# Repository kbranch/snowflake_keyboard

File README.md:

# Snowflake Keyboard

This is a weird, tightly spaced split keyboard that I designed to be very specific to my needs. It uses 17x16 mm key spacing rather than the standard 19x19 mm (inspired by [this post](https://www.reddit.com/r/ErgoMechKeyboards/comments/hudjyt/current_research_on_ergonomics_keyboard_design/)). The odd keys on the outside bottom corners are meant to be pressed with the pinky's knuckle rather than a fingertip. I haven't included every detail necessary to build the whole keyboard since it's so specific to my needs, but I'm happy to share and/or answer questions if somebody is interested in more detail for some reason.

The original CAD files are public on OnShape: [Case](https://cad.onshape.com/documents/9b32c1e8e8106ea44925f1b6/w/90cc6aeac4d327d0808a83e7/e/3e782787b37f9a3620b3203b) and [Keycaps](https://cad.onshape.com/documents/7a9b7e869b26a13f2521e861/w/94ad519ba1de32380f27d44b/e/4a5e31582eda700c8368bdb9). Generating the keycap legends is a pretty manual and sometimes fiddly process. I believe I included copies of all of the STLs I used, but I may have forgotten a few. 3mf files are included for the keycaps and legends, which should load into PrusaSlicer with all models in their correct quantities and print settings ready to go for a Prusa i3 MK3S.

All 3D printed parts are designed to be printed without support. I used manual mid-print color changes to embed the LED diffuser pieces into the case and for the keycap legends. M2 screws and nuts hold the PCB and plate to the case, and M3 screws and nuts hold the case halves and palm rests together. Little o-rings sit between the plate and case.

I used USB-C for both the actual USB connector and the board to board connection. I repurposed some [USB-A to USB-C adapters](https://www.amazon.com/gp/product/B07VCZV3R4/ref=ppx_yo_dt_b_asin_title_o09_s00?ie=UTF8&psc=1) to use as panel mount USB-C connectors. I ended up needing to grind the fronts down a bit to allow for cables to snap in fully through the case thickness.

The referenced QMK version includes a small tweak to allow the brightness of the indicator LEDs to follow the regular LED animation brightness. The LEDs are set up to indicate the active layer and the status of num, caps and scroll lock - they're not intended for flashy animations.

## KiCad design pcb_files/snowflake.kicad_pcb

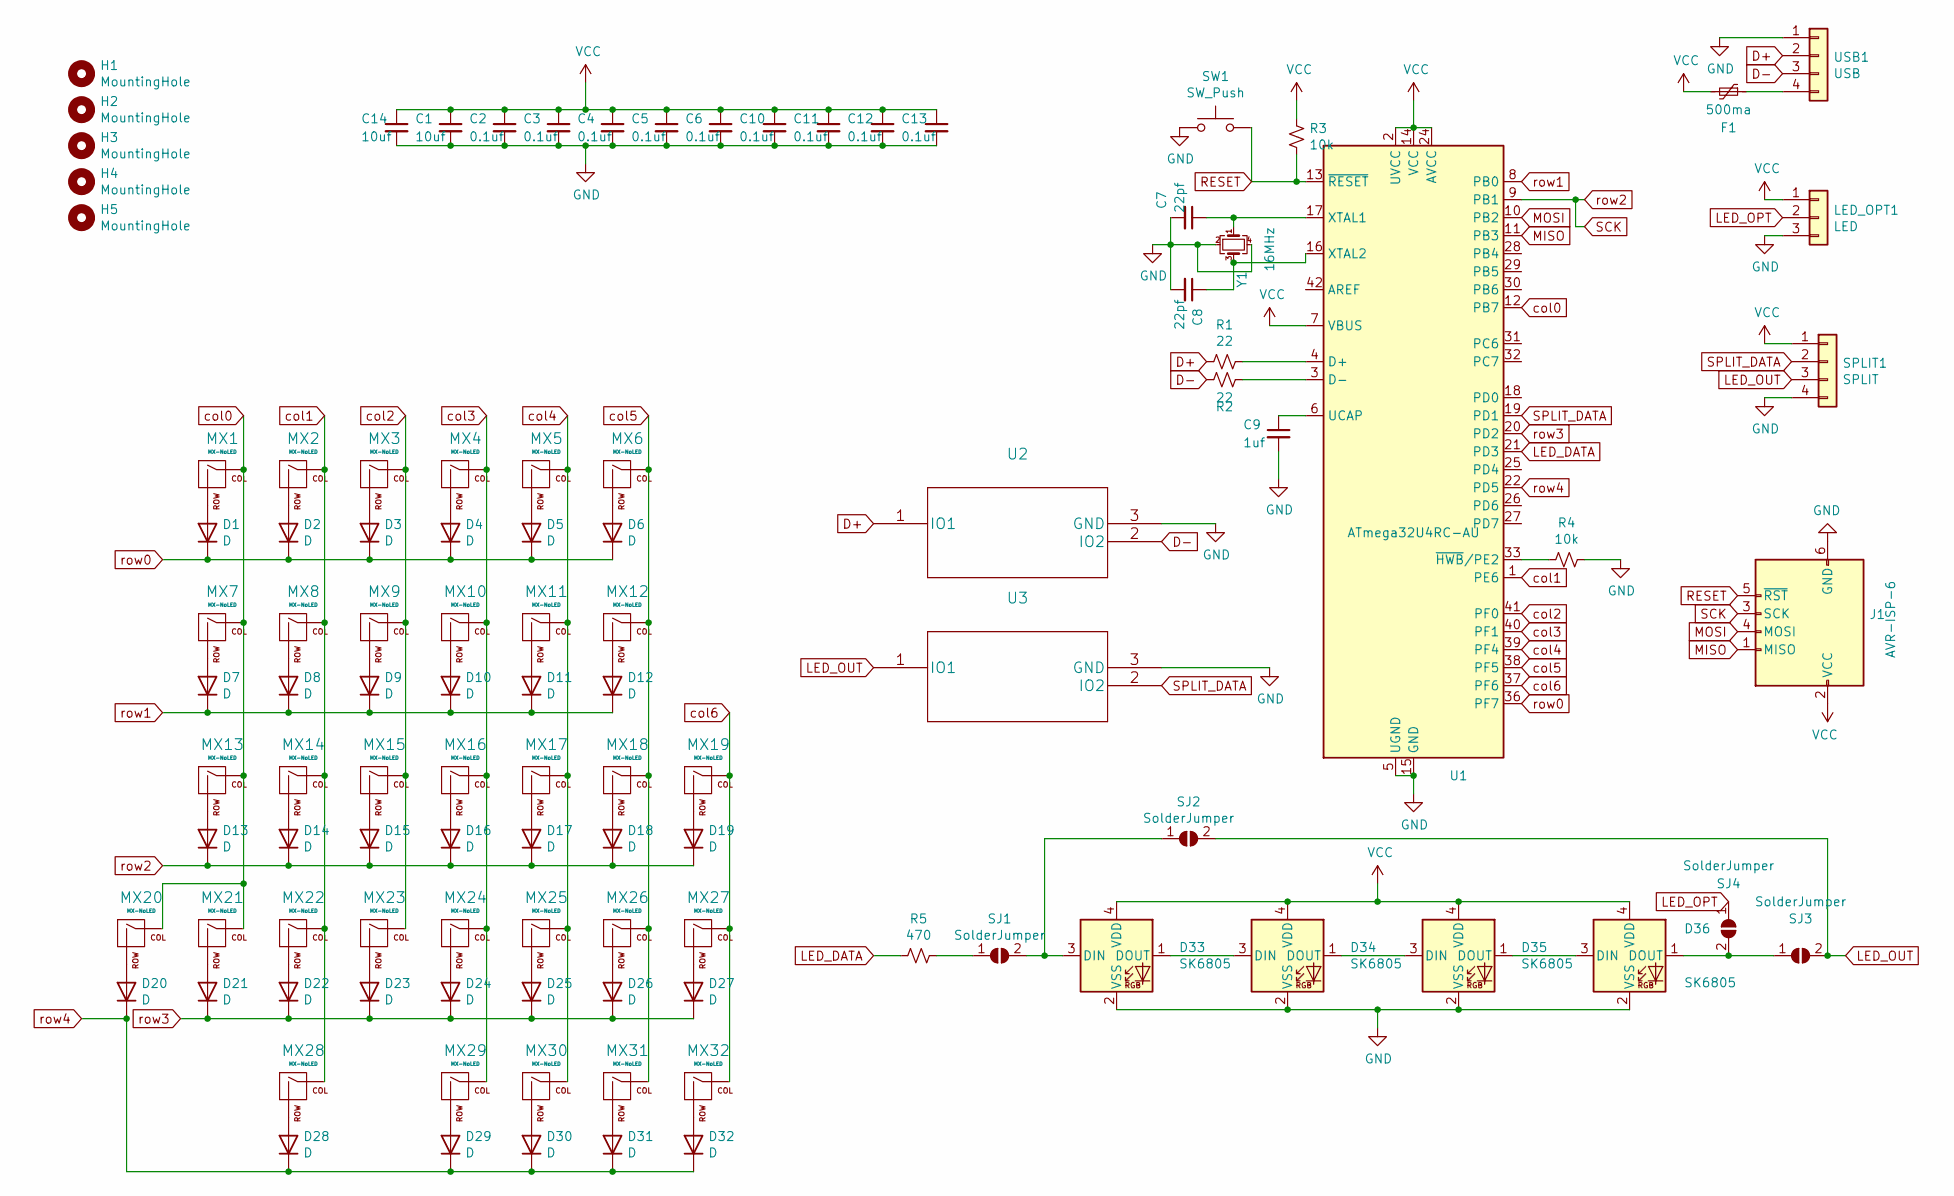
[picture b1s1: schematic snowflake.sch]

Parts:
C1, C14: 10uf; C_0603_1608Metric_Pad1.08x0.95mm_HandSolder
C2, C3, C4, C5, C6, C10, C11, C12, C13: 0.1uf; C_0603_1608Metric_Pad1.08x0.95mm_HandSolder
C7, C8: 22pf; C_0603_1608Metric_Pad1.08x0.95mm_HandSolder
C9: 1uf; C_0603_1608Metric_Pad1.08x0.95mm_HandSolder
D1, D2, D3, D4, D5, D6, D7, D8, D9, D10, D11, D12, D13, D14, D15, D16, D17, D18, D19, D20, D21, D22, D23, D24, D25, D26, D27, D28, D29, D30, D31, D32: D; D_SOD-123
D33, D34, D35, D36: SK6805; LED_SK6805_PLCC4_2.4x2.7mm_P1.3mm
F1: 500ma; Fuse_0805_2012Metric_Castellated
H1, H2, H3, H4, H5: MountingHole; MountingHole_2.2mm_M2
J1: AVR-ISP-6; PinHeader_2x03_P2.54mm_Vertical
LED_OPT1: LED; PinHeader_1x03_P2.54mm_Horizontal
MX1, MX2, MX3, MX4, MX5, MX6, MX7, MX8, MX9, MX10, MX11, MX12, MX13, MX14, MX15, MX16, MX17, MX18, MX19, MX20, MX21, MX22, MX23, MX24, MX25, MX26, MX27, MX28, MX29, MX30, MX31, MX32: MX-NoLED; Kailh_socket_MX
R1, R2: 22; R_0603_1608Metric_Pad0.98x0.95mm_HandSolder
R3, R4: 10k; R_0603_1608Metric_Pad0.98x0.95mm_HandSolder
R5: 470; R_0603_1608Metric_Pad0.98x0.95mm_HandSolder
SJ1, SJ2, SJ3, SJ4: SolderJumper; SolderJumper-2_P1.3mm_Open_RoundedPad1.0x1.5mm
SPLIT1: SPLIT; PinHeader_1x04_P2.54mm_Horizontal
SW1: SW_Push; SW_Push_SPST_NO_Alps_SKRK
U1: ATmega32U4RC-AU; TQFP-44_10x10mm_P0.8mm
U2, U3: TPD2E2U06DCKR
USB1: USB; PinHeader_1x04_P2.54mm_Horizontal
Y1: 16MHz; Crystal_SMD_3225-4Pin_3.2x2.5mm_HandSoldering

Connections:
D+: R1.2, U2.1 (IO1), USB1.2
D-: R2.2, U2.2 (IO2), USB1.3
GND: C1.2, C2.2, C3.2, C4.2, C5.2, C6.2, C7.2, C8.2, C9.2, C10.2, C11.2, C12.2, C13.2, C14.2, D33.2 (VSS), D34.2 (VSS), D35.2 (VSS), D36.2 (VSS), J1.6 (GND), LED_OPT1.3, R4.1, SPLIT1.4, SW1.1, U1.5 (UGND), U1.15 (GND), U1.23 (GND), U1.35 (GND), U1.43 (GND), U2.3 (GND), U3.3 (GND), USB1.1, Y1.2, Y1.4; also elsewhere on the board
LED_DATA: R5.2, U1.21 (PD3)
LED_OPT: LED_OPT1.2, SJ4.1 (A)
LED_OUT: SJ2.2 (B), SJ3.2 (B), SPLIT1.3, U3.1 (IO1)
MISO: J1.1 (MISO), U1.11 (PB3); also elsewhere on the board
MOSI: J1.4 (MOSI), U1.10 (PB2); also elsewhere on the board
unnamed: C7.1, U1.17 (XTAL1), Y1.1
unnamed: C8.1, U1.16 (XTAL2), Y1.3
unnamed: C9.1, U1.6 (UCAP)
unnamed: D1.2 (A), MX1.2 (ROW)
unnamed: D2.2 (A), MX2.2 (ROW)
unnamed: D3.2 (A), MX3.2 (ROW)
unnamed: D4.2 (A), MX4.2 (ROW)
unnamed: D5.2 (A), MX5.2 (ROW)
unnamed: D6.2 (A), MX6.2 (ROW)
unnamed: D7.2 (A), MX7.2 (ROW)
unnamed: D8.2 (A), MX8.2 (ROW)
unnamed: D9.2 (A), MX9.2 (ROW)
unnamed: D10.2 (A), MX10.2 (ROW)
unnamed: D11.2 (A), MX11.2 (ROW)
unnamed: D12.2 (A), MX12.2 (ROW)
unnamed: D13.2 (A), MX13.2 (ROW)
unnamed: D14.2 (A), MX14.2 (ROW)
unnamed: D15.2 (A), MX15.2 (ROW)
unnamed: D16.2 (A), MX16.2 (ROW)
unnamed: D17.2 (A), MX17.2 (ROW)
unnamed: D18.2 (A), MX18.2 (ROW)
unnamed: D19.2 (A), MX19.2 (ROW)
unnamed: D20.2 (A), MX20.2 (ROW)
unnamed: D21.2 (A), MX21.2 (ROW)
unnamed: D22.2 (A), MX22.2 (ROW)
unnamed: D23.2 (A), MX23.2 (ROW)
unnamed: D24.2 (A), MX24.2 (ROW)
unnamed: D25.2 (A), MX25.2 (ROW)
unnamed: D26.2 (A), MX26.2 (ROW)
unnamed: D27.2 (A), MX27.2 (ROW)
unnamed: D28.2 (A), MX28.2 (ROW)
unnamed: D29.2 (A), MX29.2 (ROW)
unnamed: D30.2 (A), MX30.2 (ROW)
unnamed: D31.2 (A), MX31.2 (ROW)
unnamed: D32.2 (A), MX32.2 (ROW)
unnamed: D33.1 (DOUT), D34.3 (DIN)
unnamed: D33.3 (DIN), SJ1.2 (B), SJ2.1 (A)
unnamed: D34.1 (DOUT), D35.3 (DIN)
unnamed: D35.1 (DOUT), D36.3 (DIN)
unnamed: D36.1 (DOUT), SJ3.1 (A), SJ4.2 (B)
unnamed: F1.1, USB1.4
unnamed: R1.1, U1.4 (D+)
unnamed: R2.1, U1.3 (D-)
unnamed: R4.2, U1.33 (~HWB~/PE2)
unnamed: R5.1, SJ1.1 (A)
RESET: J1.5 (~RST), R3.1, SW1.2, U1.13 (~RESET); also elsewhere on the board
SCK: D13.1 (K), D14.1 (K), D15.1 (K), D16.1 (K), D17.1 (K), D18.1 (K), D19.1 (K), J1.3 (SCK), U1.9 (PB1); also elsewhere on the board
SPLIT_DATA: SPLIT1.2, U1.19 (PD1), U3.2 (IO2)
VCC: C1.1, C2.1, C3.1, C4.1, C5.1, C6.1, C10.1, C11.1, C12.1, C13.1, C14.1, D33.4 (VDD), D34.4 (VDD), D35.4 (VDD), D36.4 (VDD), F1.2, J1.2 (VCC), LED_OPT1.1, R3.2, SPLIT1.1, U1.2 (UVCC), U1.7 (VBUS), U1.14 (VCC), U1.24 (AVCC), U1.34 (VCC), U1.44 (AVCC); also elsewhere on the board
col0: MX1.1 (COL), MX7.1 (COL), MX13.1 (COL), MX20.1 (COL), MX21.1 (COL), U1.12 (PB7)
col1: MX2.1 (COL), MX8.1 (COL), MX14.1 (COL), MX22.1 (COL), MX28.1 (COL), U1.1 (PE6)
col2: MX3.1 (COL), MX9.1 (COL), MX15.1 (COL), MX23.1 (COL), U1.41 (PF0)
col3: MX4.1 (COL), MX10.1 (COL), MX16.1 (COL), MX24.1 (COL), MX29.1 (COL), U1.40 (PF1)
col4: MX5.1 (COL), MX11.1 (COL), MX17.1 (COL), MX25.1 (COL), MX30.1 (COL), U1.39 (PF4)
col5: MX6.1 (COL), MX12.1 (COL), MX18.1 (COL), MX26.1 (COL), MX31.1 (COL), U1.38 (PF5)
col6: MX19.1 (COL), MX27.1 (COL), MX32.1 (COL), U1.37 (PF6)
row0: D1.1 (K), D2.1 (K), D3.1 (K), D4.1 (K), D5.1 (K), D6.1 (K), U1.36 (PF7)
row1: D7.1 (K), D8.1 (K), D9.1 (K), D10.1 (K), D11.1 (K), D12.1 (K), U1.8 (PB0)
row3: D21.1 (K), D22.1 (K), D23.1 (K), D24.1 (K), D25.1 (K), D26.1 (K), D27.1 (K), U1.20 (PD2)
row4: D20.1 (K), D28.1 (K), D29.1 (K), D30.1 (K), D31.1 (K), D32.1 (K), U1.22 (PD5)

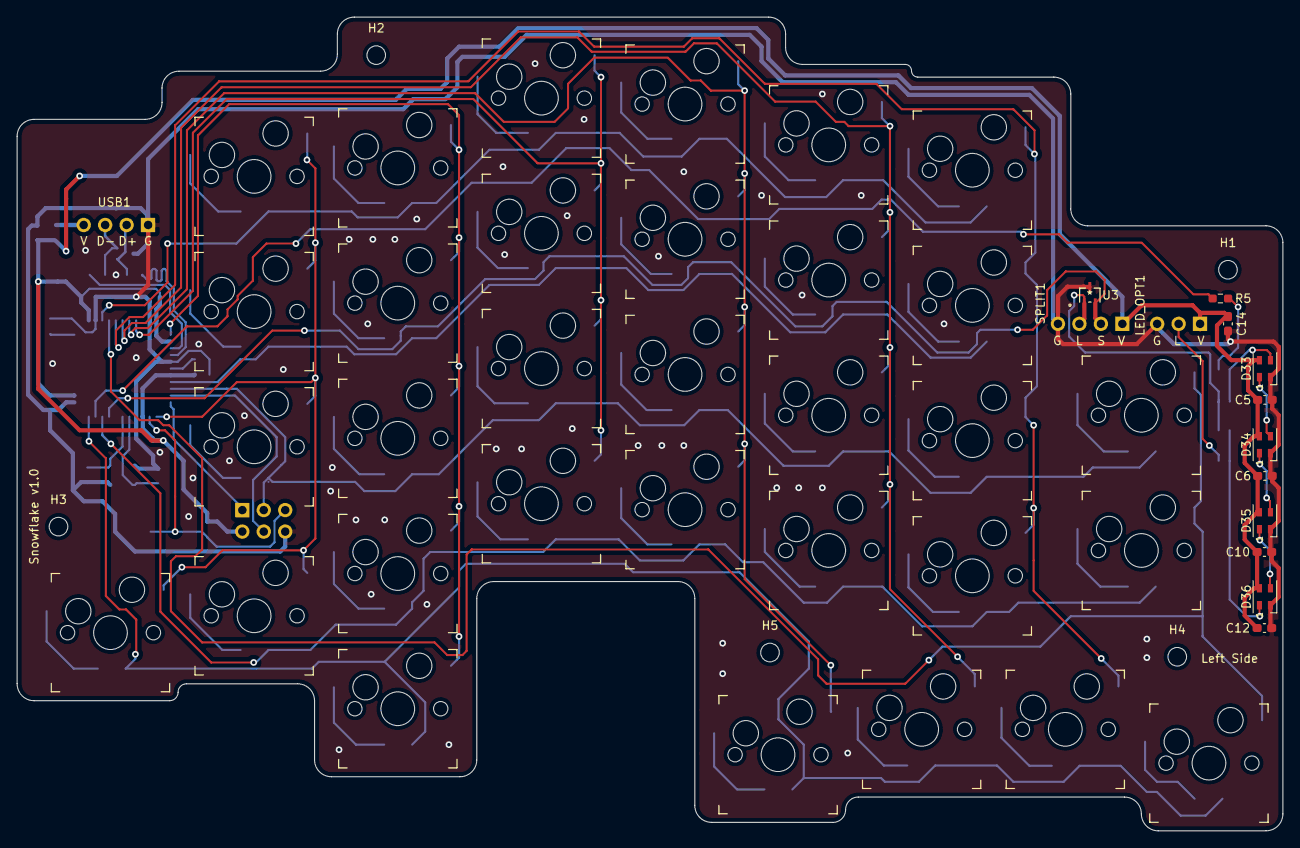
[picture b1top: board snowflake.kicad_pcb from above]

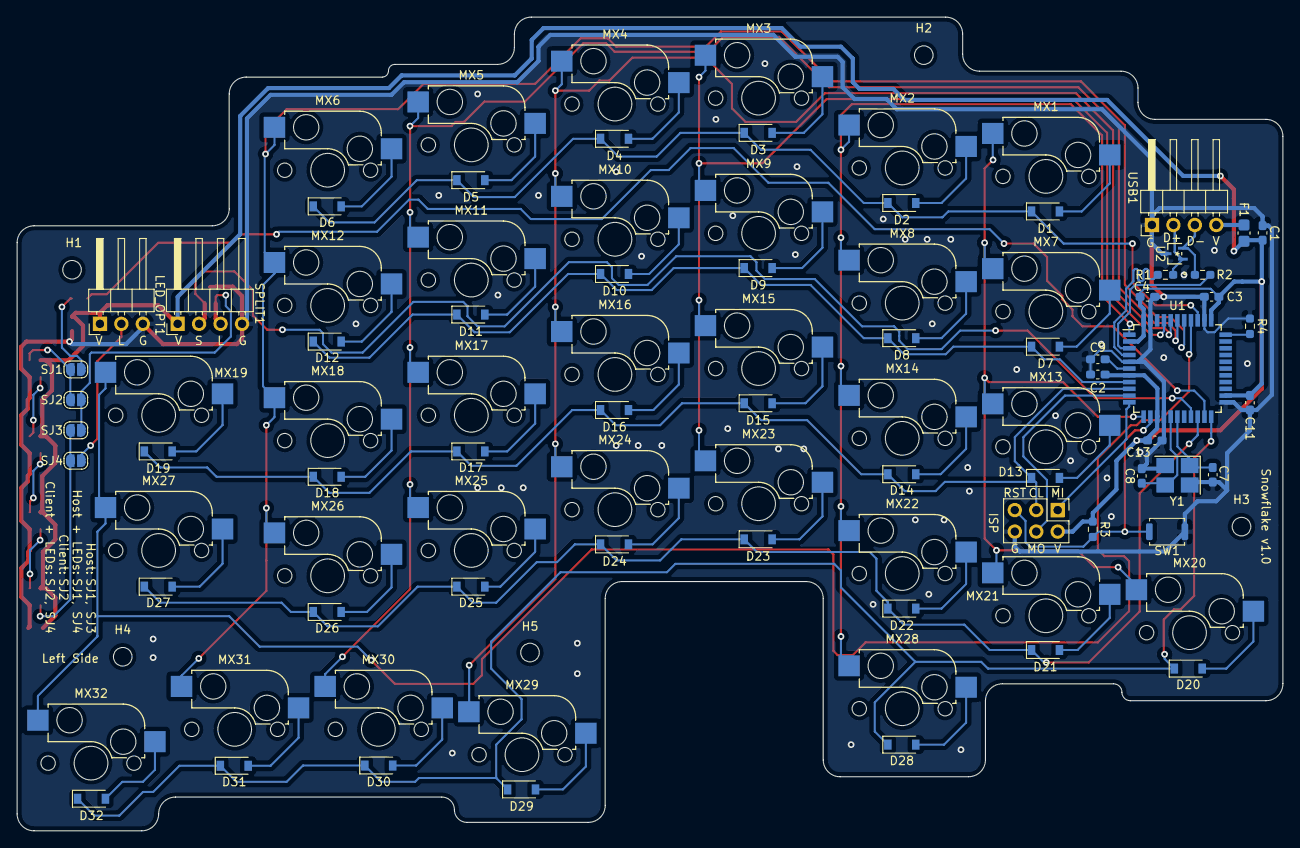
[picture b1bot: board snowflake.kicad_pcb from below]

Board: 2 copper layers, 149.8 x 96.3 mm, 106 parts (58 on the bottom side), 68 nets.

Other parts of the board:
ISP: AVR-ISP-6; PinHeader_2x03_P2.54mm_Vertical

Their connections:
GND: ISP.6; also elsewhere on the board
MISO: ISP.1; also elsewhere on the board
MOSI: ISP.4; also elsewhere on the board
RESET: ISP.5; also elsewhere on the board
SCK: ISP.3; also elsewhere on the board
VCC: ISP.2; also elsewhere on the board

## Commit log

2021-06-19 Added a couple pictures
2021-06-19 Renamed the 3mf files

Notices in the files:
parts and their libraries:
Copyright 2016 Accelerated Designs. All rights reserved.
